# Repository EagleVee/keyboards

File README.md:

# Ortholinear keyboard but still use normal keycaps set

WIP

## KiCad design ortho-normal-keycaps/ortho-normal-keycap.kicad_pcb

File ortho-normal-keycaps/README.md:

# Ortholinear keyboard with normal keycaps set

---
### Work in progress

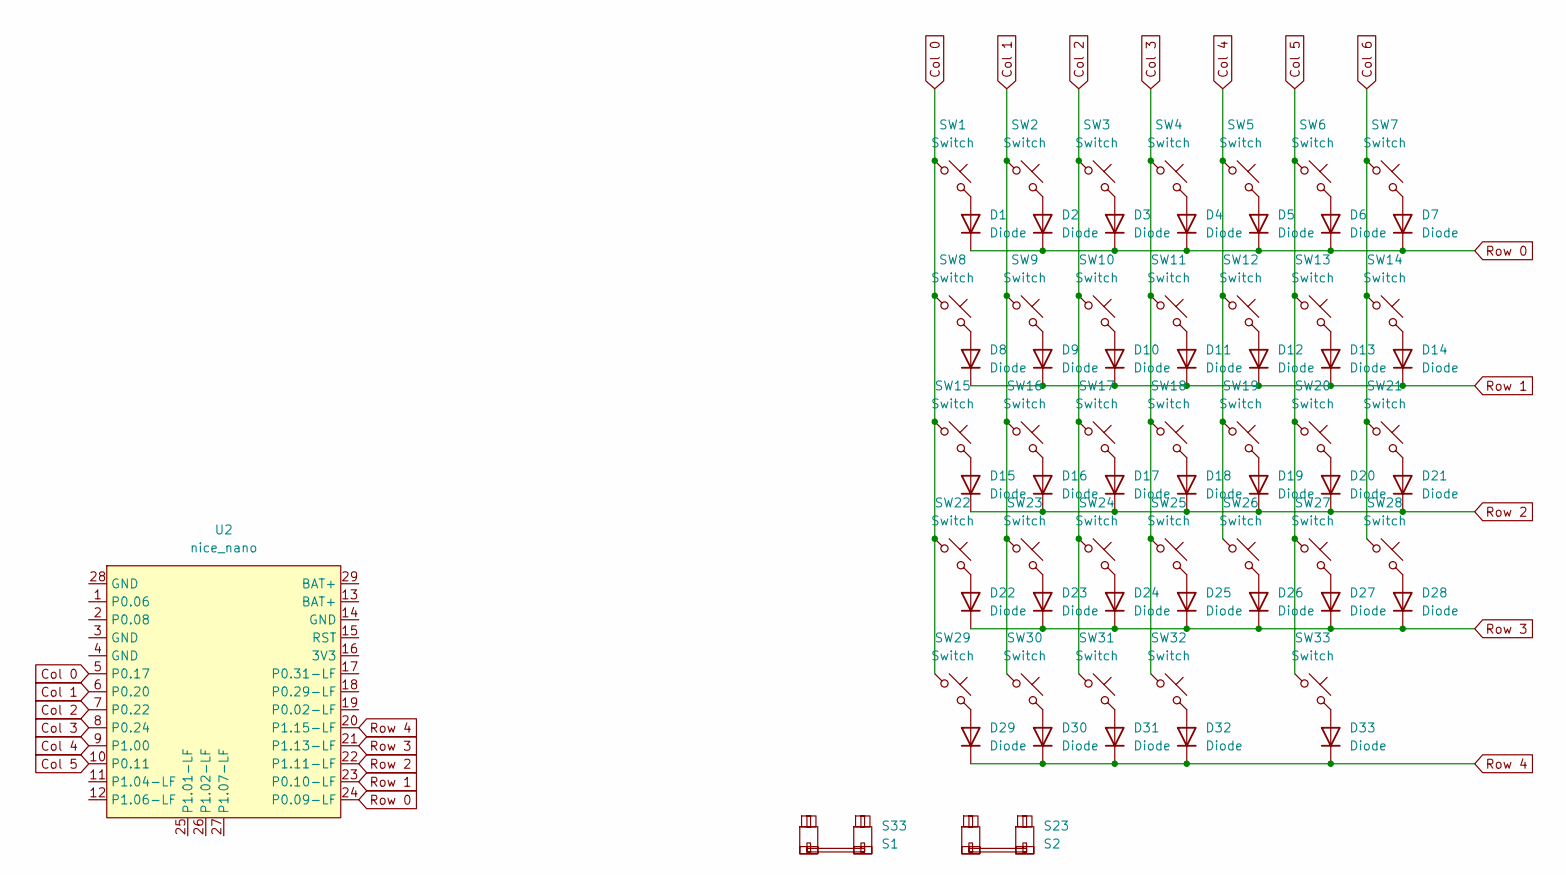
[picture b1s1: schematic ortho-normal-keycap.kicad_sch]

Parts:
D1, D2, D3, D4, D5, D6, D7, D8, D9, D10, D11, D12, D13, D14, D15, D16, D17, D18, D19, D20, D21, D22, D23, D24, D25, D26, D27, D28, D29, D30, D31, D32, D33: Diode; D_SOD-123
S23: S2; STAB_MX_2.75u
S33: S1; STAB_MX_2.25u
SW1, SW2, SW3, SW4, SW5, SW6, SW7, SW8, SW10, SW11, SW12, SW13, SW14, SW15, SW17, SW18, SW19, SW20, SW21, SW22, SW23, SW24, SW25, SW26, SW27, SW28, SW29, SW33: Switch; SW_MX_1u
SW9: Switch; SW_MX_1.5u
SW16: Switch; SW_MX_CapsLock
SW30, SW31, SW32: Switch; SW_MX_1.25u
U2: nice_nano; nice_nano_AH_USBup

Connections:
Col 0: SW1.1, SW8.1, SW15.1, SW22.1, SW29.1, U2.5 (P0.17)
Col 1: SW2.1, SW9.1, SW16.1, SW23.1, SW30.1, U2.6 (P0.20)
Col 2: SW3.1, SW10.1, SW17.1, SW24.1, SW31.1, U2.7 (P0.22)
Col 3: SW4.1, SW11.1, SW18.1, SW25.1, SW32.1, U2.8 (P0.24)
Col 4: SW5.1, SW12.1, SW19.1, SW26.1, U2.9 (P1.00)
Col 5: SW6.1, SW13.1, SW20.1, SW27.1, SW33.1, U2.10 (P0.11)
Col 6: SW7.1, SW14.1, SW21.1, SW28.1
unnamed: D1.2 (A), SW1.2
unnamed: D2.2 (A), SW2.2
unnamed: D3.2 (A), SW3.2
unnamed: D4.2 (A), SW4.2
unnamed: D5.2 (A), SW5.2
unnamed: D6.2 (A), SW6.2
unnamed: D7.2 (A), SW7.2
unnamed: D8.2 (A), SW8.2
unnamed: D9.2 (A), SW9.2
unnamed: D10.2 (A), SW10.2
unnamed: D11.2 (A), SW11.2
unnamed: D12.2 (A), SW12.2
unnamed: D13.2 (A), SW13.2
unnamed: D14.2 (A), SW14.2
unnamed: D15.2 (A), SW15.2
unnamed: D16.2 (A), SW16.2
unnamed: D17.2 (A), SW17.2
unnamed: D18.2 (A), SW18.2
unnamed: D19.2 (A), SW19.2
unnamed: D20.2 (A), SW20.2
unnamed: D21.2 (A), SW21.2
unnamed: D22.2 (A), SW22.2
unnamed: D23.2 (A), SW23.2
unnamed: D24.2 (A), SW24.2
unnamed: D25.2 (A), SW25.2
unnamed: D26.2 (A), SW26.2
unnamed: D27.2 (A), SW27.2
unnamed: D28.2 (A), SW28.2
unnamed: D29.2 (A), SW29.2
unnamed: D30.2 (A), SW30.2
unnamed: D31.2 (A), SW31.2
unnamed: D32.2 (A), SW32.2
unnamed: D33.2 (A), SW33.2
Row 0: D1.1 (K), D2.1 (K), D3.1 (K), D4.1 (K), D5.1 (K), D6.1 (K), D7.1 (K), U2.24 (P0.09-LF)
Row 1: D8.1 (K), D9.1 (K), D10.1 (K), D11.1 (K), D12.1 (K), D13.1 (K), D14.1 (K), U2.23 (P0.10-LF)
Row 2: D15.1 (K), D16.1 (K), D17.1 (K), D18.1 (K), D19.1 (K), D20.1 (K), D21.1 (K), U2.22 (P1.11-LF)
Row 3: D22.1 (K), D23.1 (K), D24.1 (K), D25.1 (K), D26.1 (K), D27.1 (K), D28.1 (K), U2.21 (P1.13-LF)
Row 4: D29.1 (K), D30.1 (K), D31.1 (K), D32.1 (K), D33.1 (K), U2.20 (P1.15-LF)

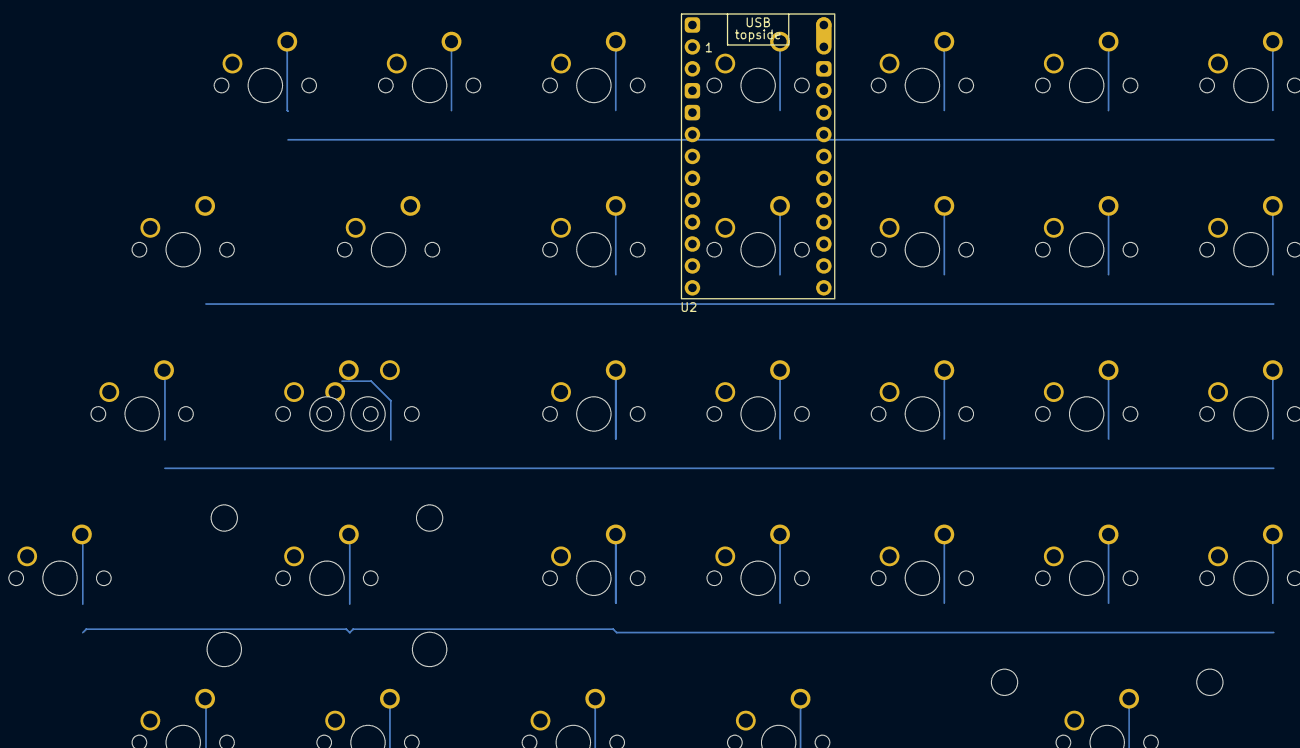
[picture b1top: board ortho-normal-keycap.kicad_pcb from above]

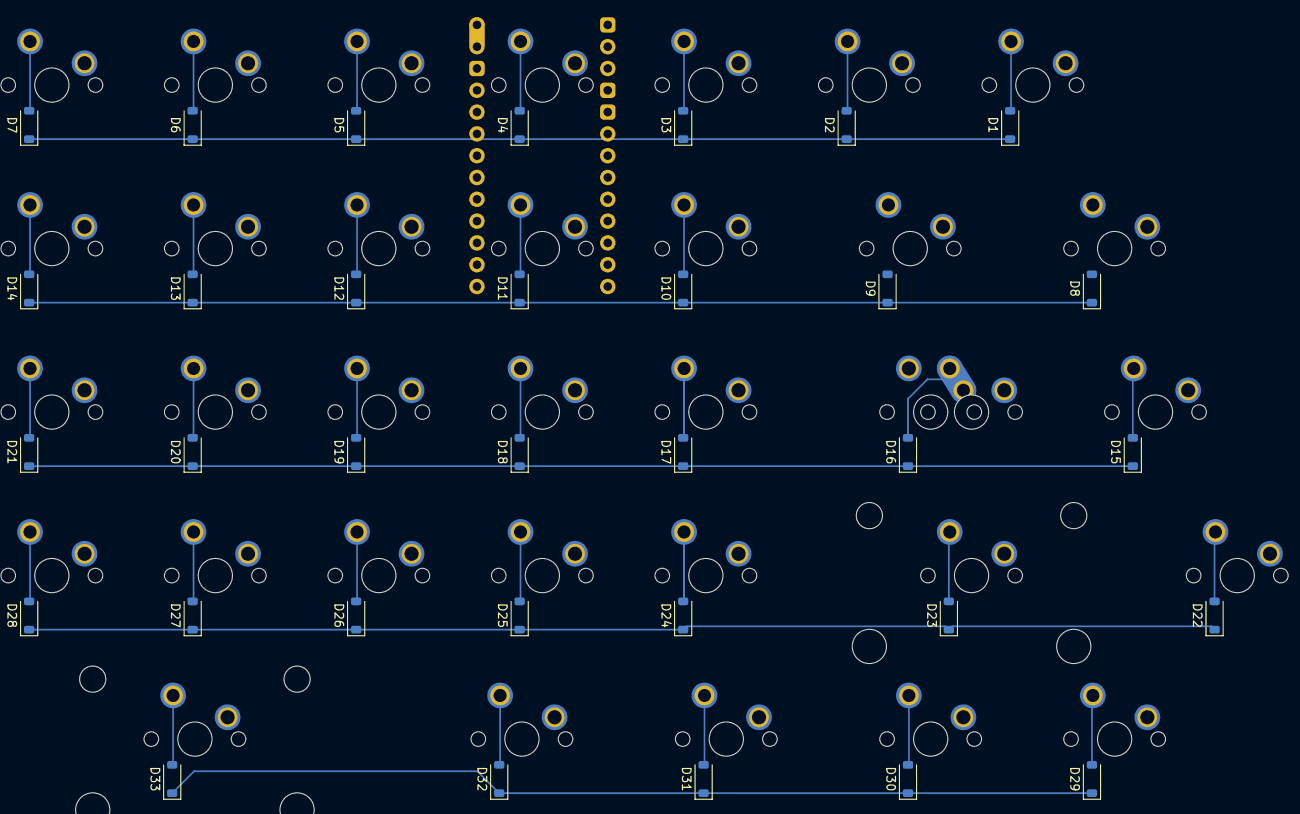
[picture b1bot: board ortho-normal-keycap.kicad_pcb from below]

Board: 2 copper layers, 69 parts (33 on the bottom side), 45 nets.

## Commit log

2023-09-27 add 60 top mount
2023-09-27 add pictures
2023-09-27 fix name
2023-09-27 fix image
2023-09-27 fix title
2023-11-29 Create LICENSE
2023-11-29 add vua-split keyboard
2023-11-29 update document
2023-11-29 update mcu document
2023-11-29 add video
2024-05-07 add pcb step
2024-08-22 add oring plateless kit
2024-08-23 add hardness
2024-08-23 add file download
2024-11-27 add ortho normal keycap pcb
2024-11-27 remove readme
2024-11-27 add readme for ortho
2024-11-27 update project
2024-12-05 replace nRF52840 with nice!nano
